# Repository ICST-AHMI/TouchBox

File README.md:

# The TouchBox MK3
A low-cost DIY interface for tracking the position multiple fingers (currently up to three) in contact with its top surface, measuring their contact areas as well as 3D (normal and lateral) forces, and providing rich vibrotactile feedback.

---
## Content

* Software:
	1. GUI - based on [MaxMSP](https://cycling74.com) (No license required to run this patch).
	2. Example Patches for vibration and optional audio feedback.
	3. [Arduino](http://arduino.cc/) code.
	4. [OpenMV](https://openmv.io/) code.

* Hardware:
	1. list of required hardware (file HardwareList.md).
	2. 3D models (STEP) and plans (PDF) - made with [OnShape](https://onshape.com).
	3. electronics schematics - made with [Eagle](https://www.autodesk.com/products/eagle/overview).

* README.md (this).

---
## Software

* Follow these steps:
	1. Refresh the list of available devices and select the Arduino (usually labeled 'usbmodem####');
	2. Toggle 'start';
	3. Reset force sensors. Press 'zeroing';
	4. For finger tracking via an openMV module, switch on 'use Video'.

* For sending the data to another application via OSC, enter ip and port numbers.

* If you need to calibrate the software, press "calibration" and once done "store".

## OSC communication protocol

### /touch/weight \<force>
force = float in [Newton]

### /touch/shear/up \<force>
force = float in [Newton]

### /touch/shear/down \<force>
force = float in [Newton]

### /touch/shear/left \<force>
force = float in [Newton]

### /touch/shear/right \<force>
force = float in [Newton]

### /touch/finger \<id> \<posX> \<posY> \<area>
id = int (identification id of finger, starts with 0)

posX = int in [pixel from center]

posY = int in [pixel from center]

area = float in [mm^2]

## Installation

For running the GUI, you need to install [MaxMSP](https://cycling74.com).
No license needed.

---
## Licenses

The Arduino and openMV code is licensed under [GNU](http://www.gnu.org/licenses/).

For everything else:  

---
## Release

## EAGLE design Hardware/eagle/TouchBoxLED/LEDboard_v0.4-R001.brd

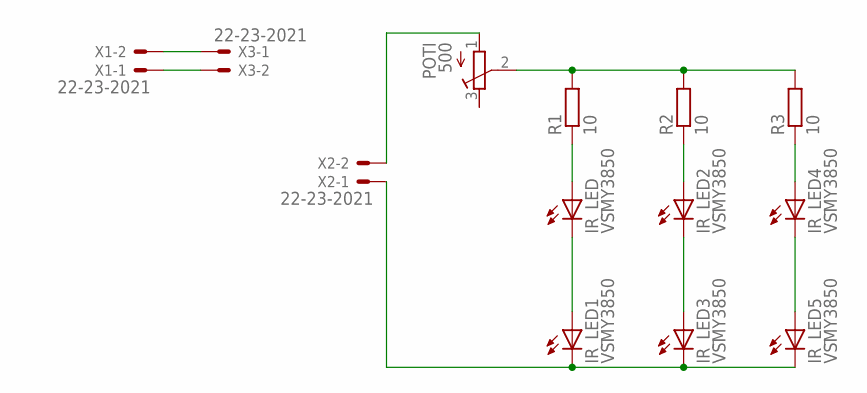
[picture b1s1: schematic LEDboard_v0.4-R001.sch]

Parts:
IR_LED, IR_LED1, IR_LED2, IR_LED3, IR_LED4, IR_LED5: VSMY3850; VSMY3850X
POTI: 500; RTRIM64Y
R1, R2, R3: 10; R0805
X1, X2, X3: 22-23-2021

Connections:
unnamed: IR_LED.2 (C), IR_LED1.1 (A)
unnamed: IR_LED.1 (A), R1.1
unnamed: IR_LED2.2 (C), IR_LED3.1 (A)
unnamed: IR_LED2.1 (A), R2.1
unnamed: IR_LED4.2 (C), IR_LED5.1 (A)
unnamed: IR_LED4.1 (A), R3.1
unnamed: POTI.2 (S), R1.2, R2.2, R3.2
unnamed: IR_LED1.2 (C), IR_LED3.2 (C), IR_LED5.2 (C), X2.1
unnamed: POTI.1 (A), X2.2
unnamed: X1.2, X3.1
unnamed: X1.1, X3.2

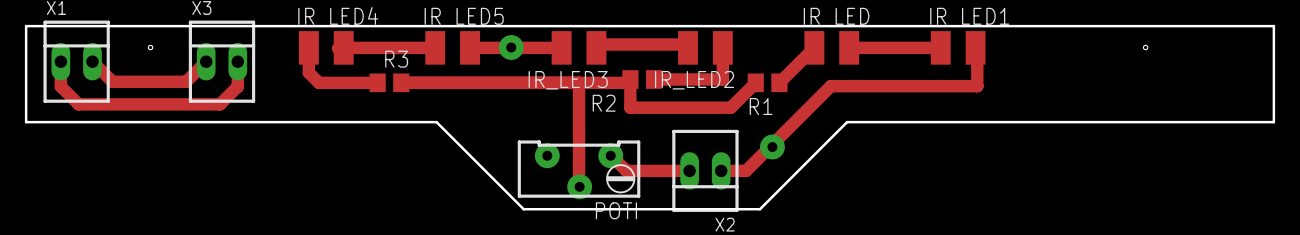
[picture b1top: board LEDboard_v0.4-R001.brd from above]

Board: 2 copper layers, 100.3 x 14.7 mm, 13 parts (0 on the bottom side), 11 nets.

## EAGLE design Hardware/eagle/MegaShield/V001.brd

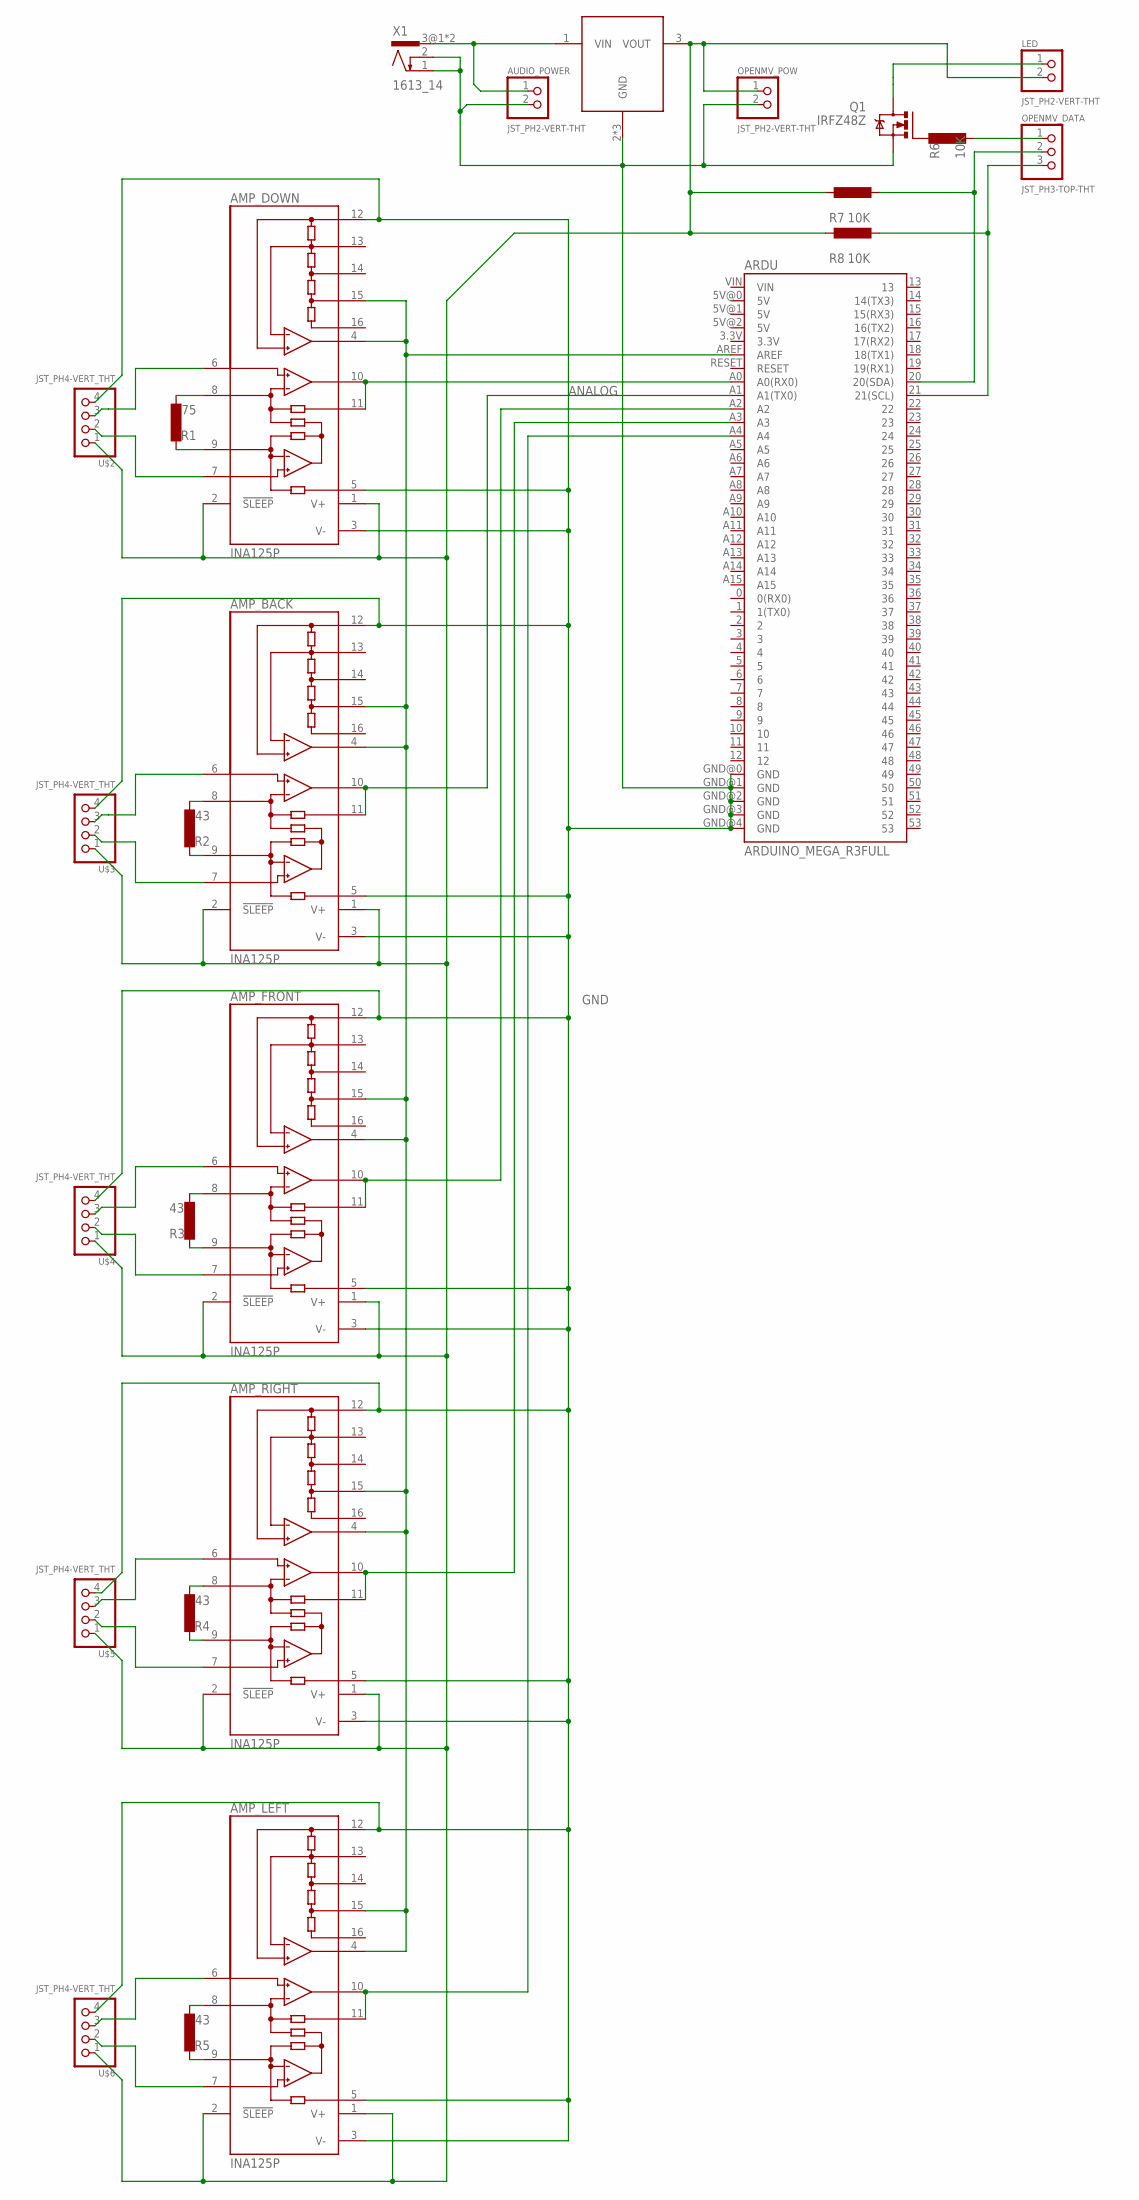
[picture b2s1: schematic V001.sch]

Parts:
AMP_BACK: INA125P; DIL16
AMP_DOWN: INA125P; DIL16
AMP_FRONT: INA125P; DIL16
AMP_LEFT: INA125P; DIL16
AMP_RIGHT: INA125P; DIL16
ARDU: ARDUINO_MEGA_R3FULL; ARDUINO_MEGA
AUDIO_POWER: JST_PH2-VERT-THT; B2B-PH-K-S
LED: JST_PH2-VERT-THT; B2B-PH-K-S
OPENMV_DATA: JST_PH3-TOP-THT; B3B-PH-K-S
OPENMV_POW: JST_PH2-VERT-THT; B2B-PH-K-S
Q1: IRFZ48Z; TO220BH
R1: 75; 0207/10
R2, R3, R4, R5: 43; 0207/10
R6, R7, R8: 10K; 0207/10
U$1: TL780; TO254P1651X1067X470-3
U$2, U$3, U$4, U$5, U$6: JST_PH4-VERT_THT; B4B-PH-K-S
X1: 1613_14

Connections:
5V: AMP_BACK.1 (V+), AMP_BACK.2 (!SLEEP), AMP_DOWN.1 (V+), AMP_DOWN.2 (!SLEEP), AMP_FRONT.1 (V+), AMP_FRONT.2 (!SLEEP), AMP_LEFT.1 (V+), AMP_LEFT.2 (!SLEEP), AMP_RIGHT.1 (V+), AMP_RIGHT.2 (!SLEEP), LED.2, OPENMV_POW.1, R7.1, R8.1, U$1.3 (VOUT), U$2.1, U$3.1, U$4.1, U$5.1, U$6.1
12V: AUDIO_POWER.1, U$1.1 (VIN), X1.3@1 (3), X1.3@2 (3)
ANALOG: AMP_DOWN.10 (OUT), AMP_DOWN.11 (SENSE), ARDU.A0 (A0(RX0))
AREF: AMP_BACK.4 (REFOUT), AMP_BACK.15 (REF5), AMP_DOWN.4 (REFOUT), AMP_DOWN.15 (REF5), AMP_FRONT.4 (REFOUT), AMP_FRONT.15 (REF5), AMP_LEFT.4 (REFOUT), AMP_LEFT.15 (REF5), AMP_RIGHT.4 (REFOUT), AMP_RIGHT.15 (REF5), ARDU.AREF
GND: AMP_BACK.3 (V-), AMP_BACK.5 (REF), AMP_BACK.12 (REFCOM), AMP_DOWN.3 (V-), AMP_DOWN.5 (REF), AMP_DOWN.12 (REFCOM), AMP_FRONT.3 (V-), AMP_FRONT.5 (REF), AMP_FRONT.12 (REFCOM), AMP_LEFT.3 (V-), AMP_LEFT.5 (REF), AMP_LEFT.12 (REFCOM), AMP_RIGHT.3 (V-), AMP_RIGHT.5 (REF), AMP_RIGHT.12 (REFCOM), ARDU.GND@0 (GND), ARDU.GND@1 (GND), ARDU.GND@2 (GND), ARDU.GND@3 (GND), ARDU.GND@4 (GND), AUDIO_POWER.2, OPENMV_POW.2, Q1.S, U$1.2 (GND), U$1.4 (GND), U$1.4.1 (GND), U$2.4, U$3.4, U$4.4, U$5.4, U$6.4, X1.1, X1.2
unnamed: AMP_DOWN.8 (RG), R1.2
unnamed: AMP_DOWN.9 (RG), R1.1
unnamed: AMP_BACK.8 (RG), R2.2
unnamed: AMP_BACK.9 (RG), R2.1
unnamed: AMP_DOWN.6 (+IN), U$2.3
unnamed: AMP_FRONT.8 (RG), R3.2
unnamed: AMP_FRONT.9 (RG), R3.1
unnamed: AMP_FRONT.10 (OUT), AMP_FRONT.11 (SENSE), ARDU.A2
unnamed: AMP_RIGHT.8 (RG), R4.2
unnamed: AMP_RIGHT.9 (RG), R4.1
unnamed: AMP_RIGHT.10 (OUT), AMP_RIGHT.11 (SENSE), ARDU.A3
unnamed: AMP_LEFT.8 (RG), R5.2
unnamed: AMP_LEFT.9 (RG), R5.1
unnamed: AMP_LEFT.10 (OUT), AMP_LEFT.11 (SENSE), ARDU.A4
unnamed: AMP_DOWN.7 (-IN), U$2.2
unnamed: OPENMV_DATA.1, R6.2
unnamed: AMP_BACK.10 (OUT), AMP_BACK.11 (SENSE), ARDU.A1 (A1(TX0))
unnamed: AMP_BACK.6 (+IN), U$3.3
unnamed: AMP_BACK.7 (-IN), U$3.2
unnamed: AMP_FRONT.6 (+IN), U$4.3
unnamed: AMP_FRONT.7 (-IN), U$4.2
unnamed: AMP_RIGHT.6 (+IN), U$5.3
unnamed: AMP_RIGHT.7 (-IN), U$5.2
unnamed: AMP_LEFT.6 (+IN), U$6.3
unnamed: AMP_LEFT.7 (-IN), U$6.2
unnamed: Q1.G, R6.1
unnamed: LED.1, Q1.D
unnamed: ARDU.20 (20(SDA)), OPENMV_DATA.2, R7.2
unnamed: ARDU.21 (21(SCL)), OPENMV_DATA.3, R8.2

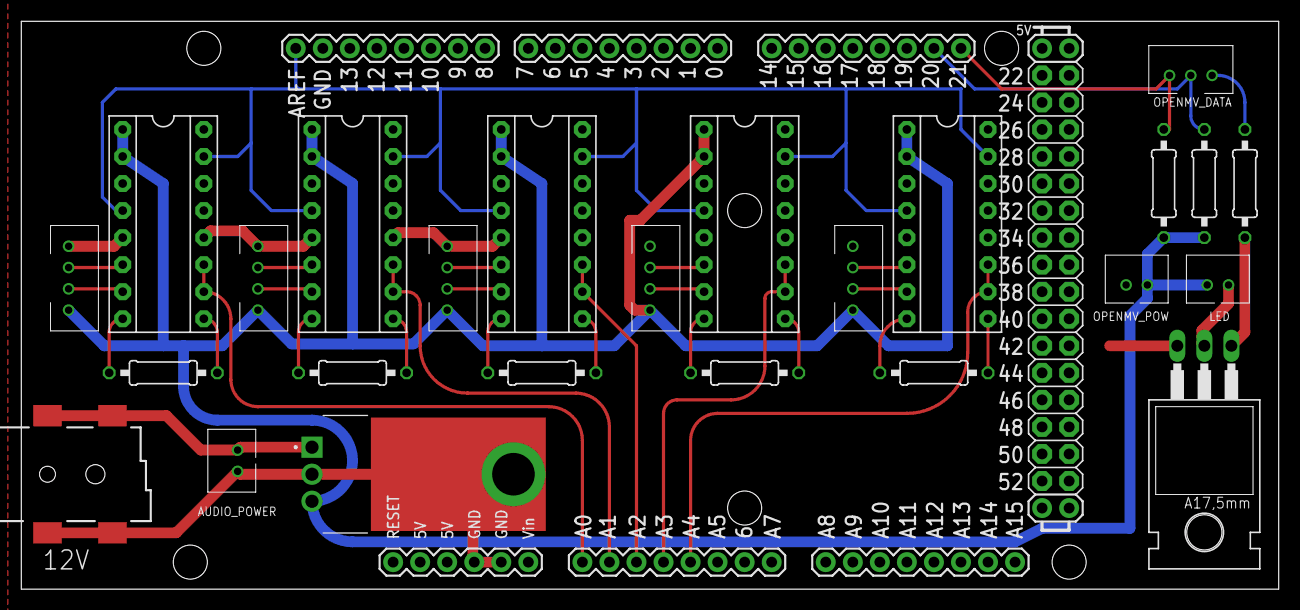
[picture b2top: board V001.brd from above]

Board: 2 copper layers, 118.1 x 53.3 mm, 26 parts (0 on the bottom side), 34 nets.

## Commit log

2018-03-21 updated readme with Zenodo DOI badge
2018-03-23 updated hardware list updated TouchBox GUI updated Readme
2018-04-17 little fixes for finger messages
2018-05-15 fixed finger message when no finger is detected
2018-05-15 new example Patches
2018-05-15 first working solution for example patches
2018-05-22 STEFANO made it work for him
2018-06-02 work in progress: refining patches and presets
2018-06-04 fixed preset bug
2018-06-04 fix the fix (there was a [t b l] missing)
2018-06-04 made a few nice presets
2018-06-05 added bandpass filter to output
2018-06-05 added a lower threshold parameter for pressing force
2018-11-16 updated presets for demo at Most Wanted Music 2018 Berlin
2018-11-16 added patch for testing actuators
2019-01-31 fixed finger measurement cleanup of codebase
2019-02-01 added additional screenshots and hardware objects that support usage of touchbox
2019-02-01 updated readme / installation instructions
2019-02-01 fixed finger issue updated GUI screenshot
2019-02-06 updated GUI
2019-08-13 updated GUI, allows to use touchbox without video stream.
2019-08-22 update to gui and new calibration
2019-08-22 fixed floating point display in GUI
2019-10-02 updated hardware list fixed arduino code for current arduino IDE (1.8.10)
2019-10-02 updated hardware list
2019-10-03 complete data chain is working
2019-10-28 added PressureBase designs
2019-10-28 added base files
2019-10-29 added IGES files
2019-10-29 added electronics files, updated base design
2019-10-31 new PressureBase design restructuring of design folder
2019-11-01 cleanup, new screen shot, readme etc
2019-11-01 app is working in its basics
2019-11-01 updated GUI screenshot
2019-11-06 updated calibration for mk02
2019-11-18 added FeatherRod plan
2020-10-13 added max dev files for testing touchbox, dev/testing files for openmv, and updates to maing TOUCHBOX.maxpat and BlobTracker_to_I2C.py
2023-07-21 Some updates for Mk03
2023-07-23 Various updates for MK3
2023-07-24 Update HardwareList.md
    removed old/added new hardware elements
2023-10-02 Working on improved version for ICMI
2023-10-05 More refinements for ICMI
2023-10-06 demo for ACM ICMI 23 ready

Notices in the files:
parts and their libraries:
SparkFun-Boards: Licensing: Creative Commons ShareAlike 4.0 International - https://creativecommons.org/licenses/by-sa/4.0
